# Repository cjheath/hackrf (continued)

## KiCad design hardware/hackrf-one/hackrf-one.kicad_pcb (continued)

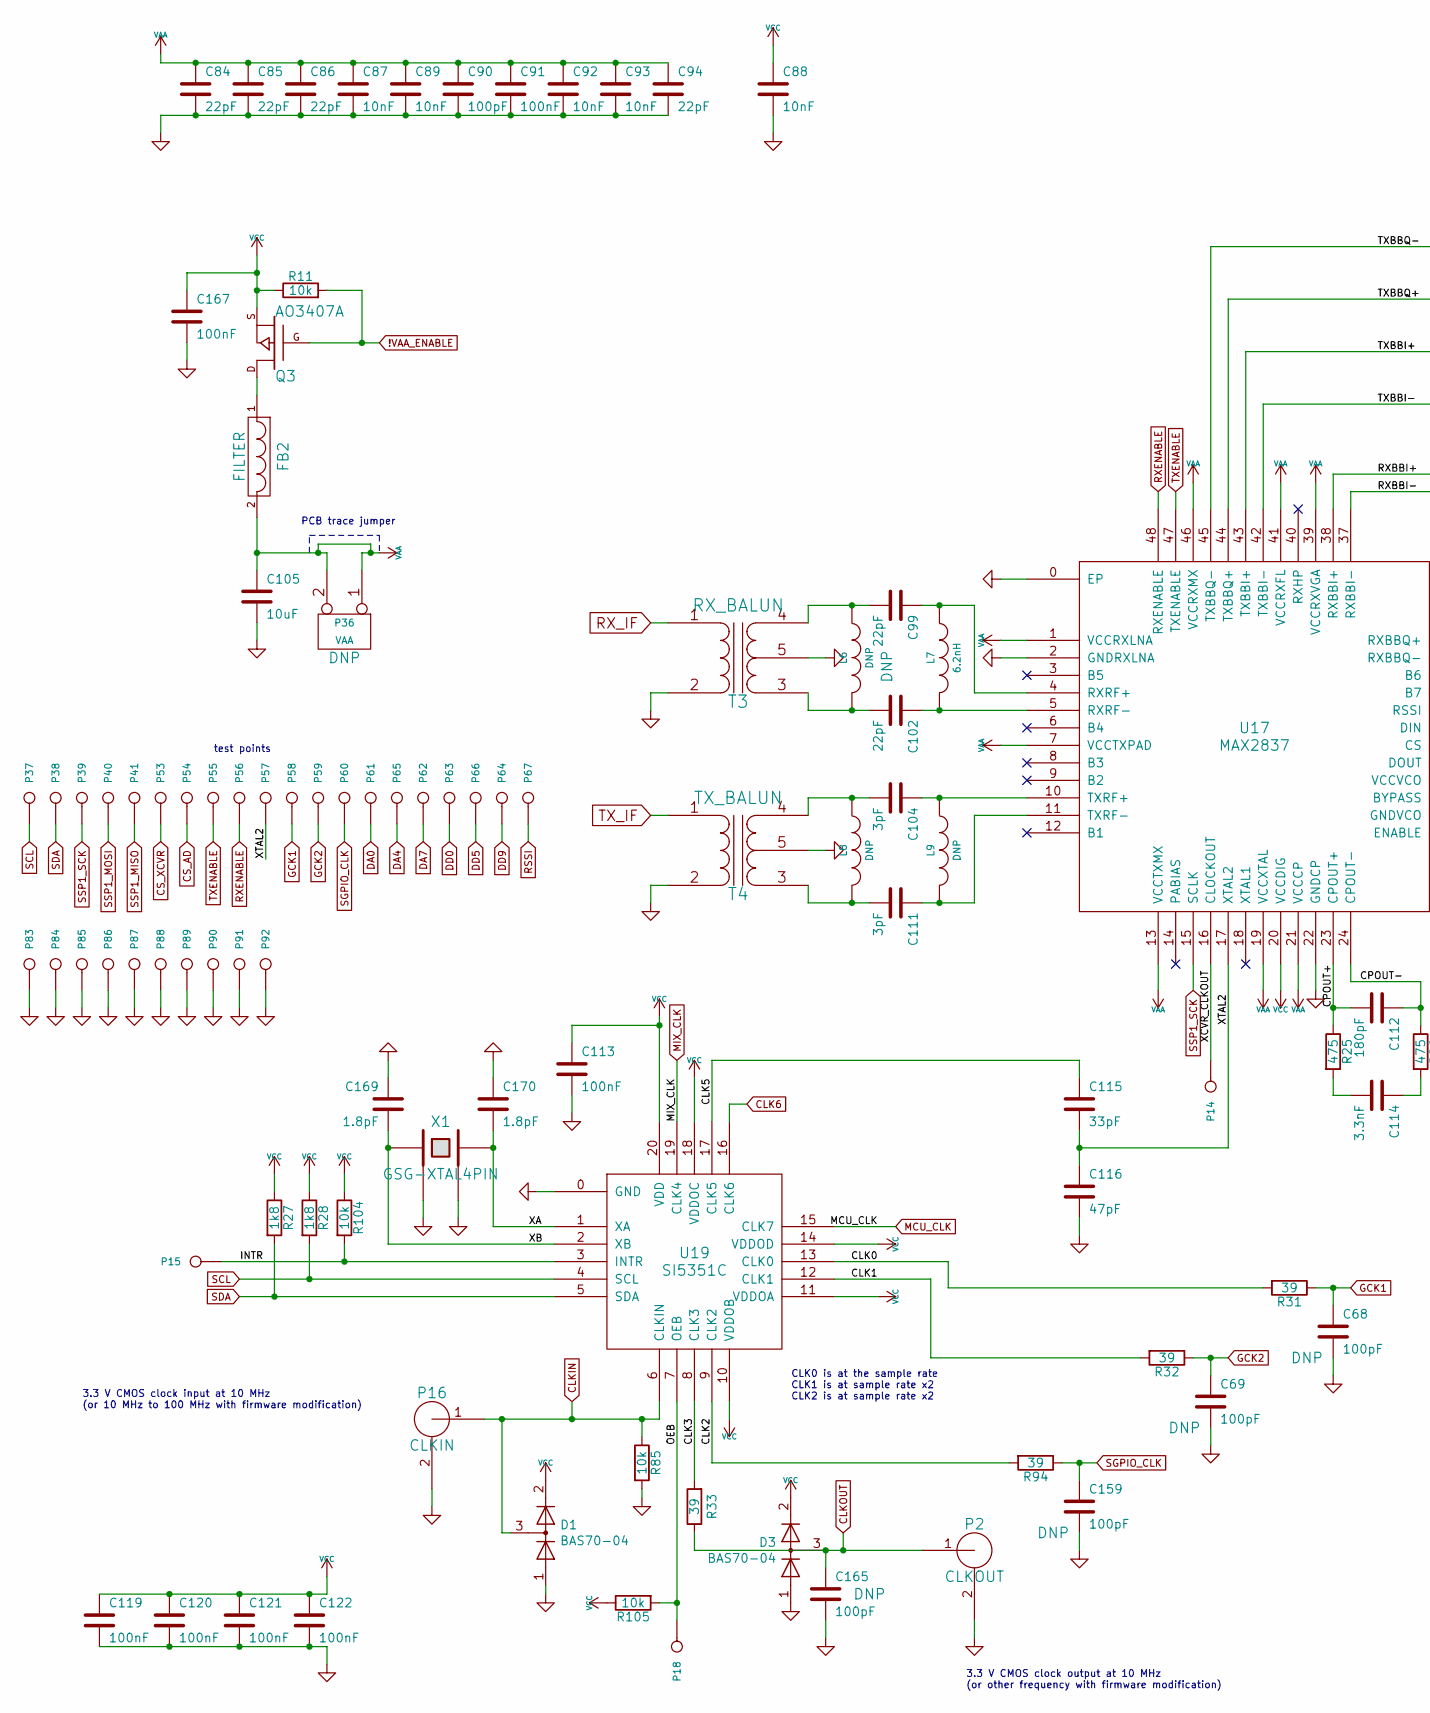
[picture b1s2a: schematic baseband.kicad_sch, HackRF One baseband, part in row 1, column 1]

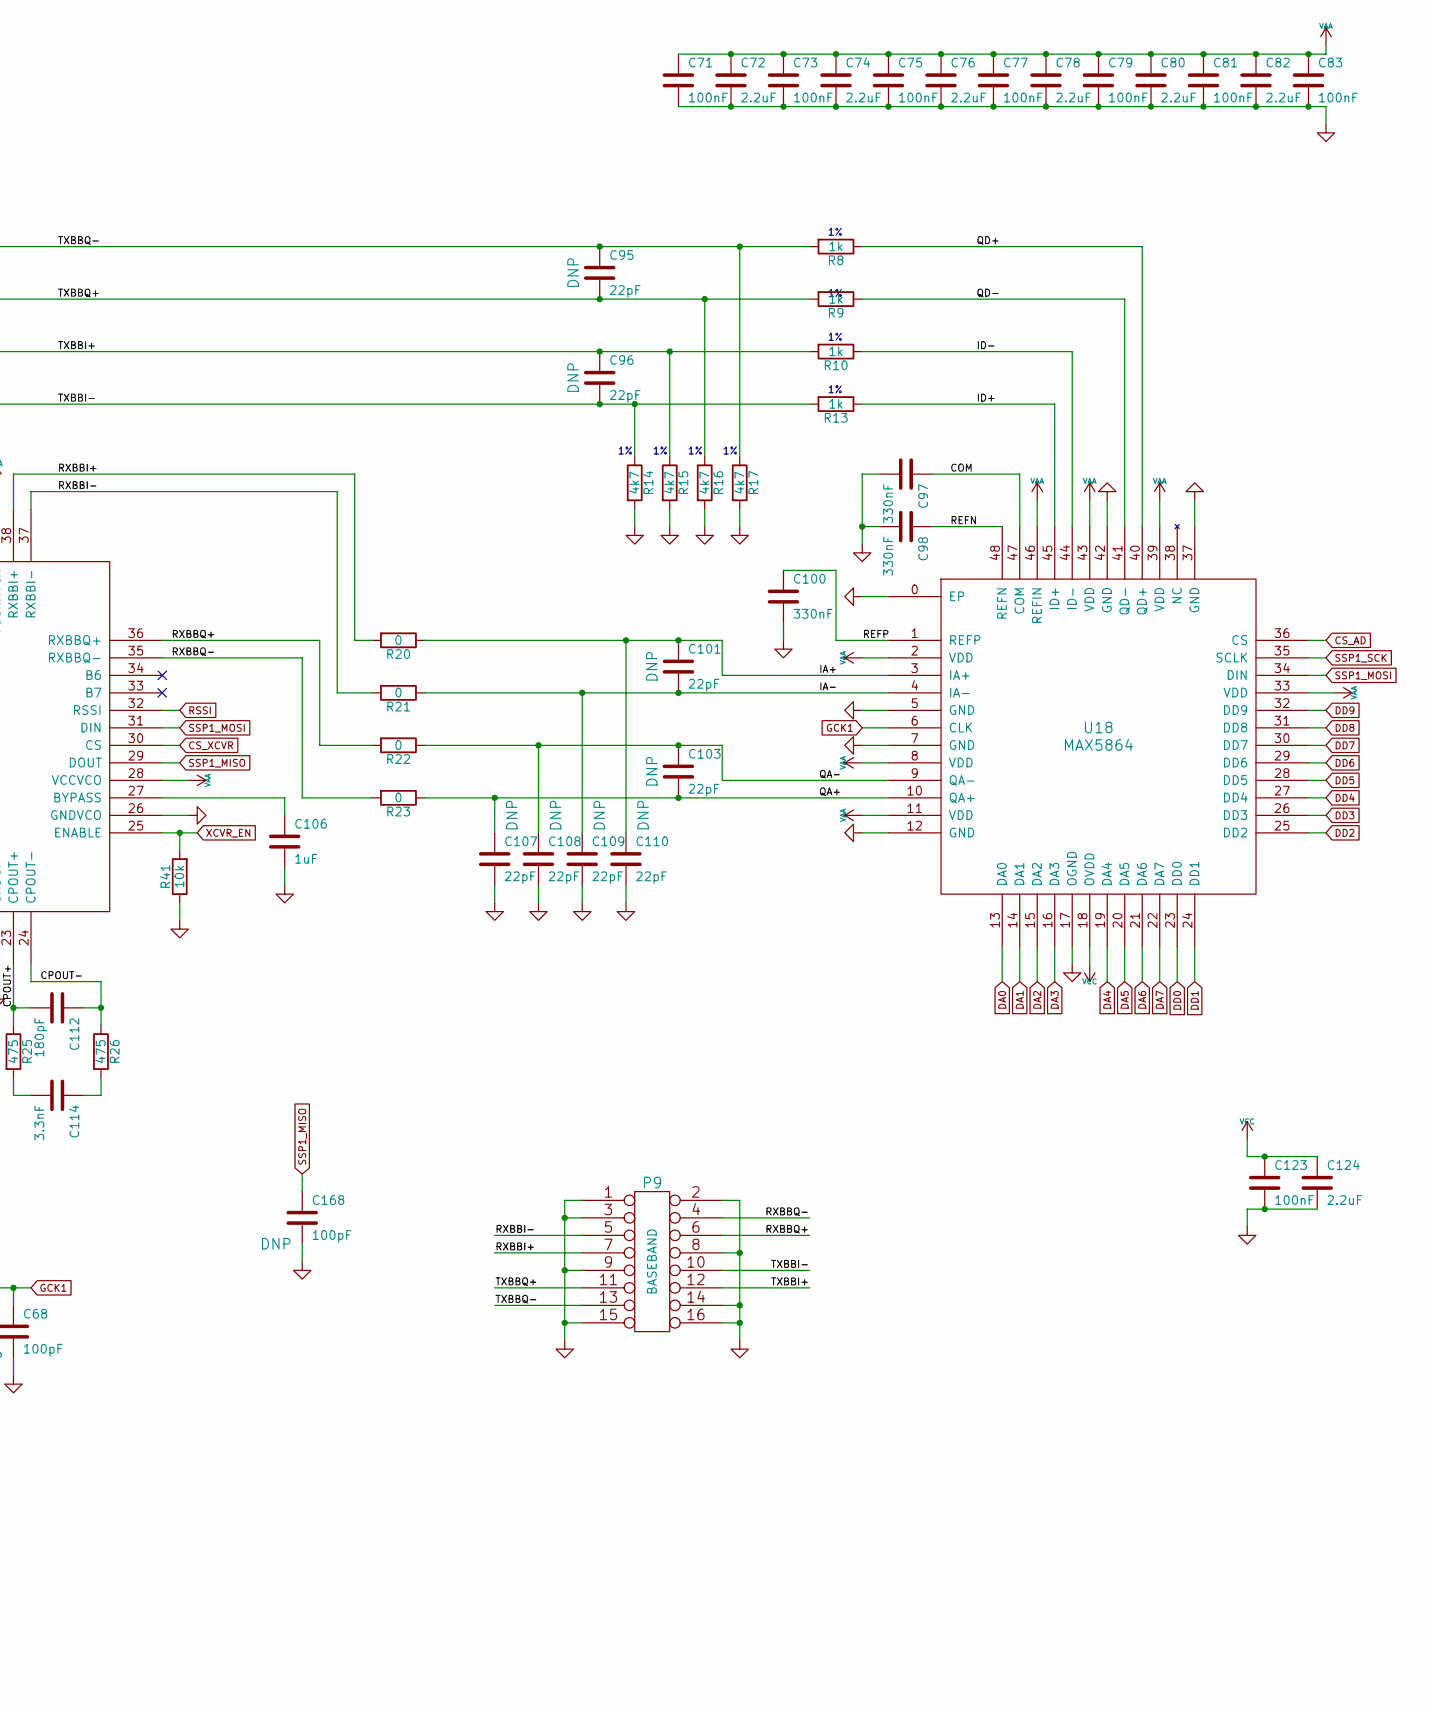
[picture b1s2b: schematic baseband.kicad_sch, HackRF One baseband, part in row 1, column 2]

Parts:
C68, C69, C90, C159, C165, C168: 100pF; GSG-0402; Part Number GRM1555C1H101JA01D
C71, C73, C75, C77, C79, C81, C83, C91, C113, C119, C120, C121, C122, C123, C167: 100nF; GSG-0402; Part Number GRM155R61A104KA01D
C72, C74, C76, C78, C80, C82, C124: 2.2uF; GSG-0402; Part Number LMK105BJ225MV-F
C84, C85, C86, C94, C95, C96, C99, C101, C102, C103, C107, C108, C109, C110: 22pF; GSG-0402; Part Number GRM1555C1H220JA01D
C87, C88, C89, C92, C93: 10nF; GSG-0402; Part Number GRM155R71C103KA01D
C97, C98, C100: 330nF; GSG-0402; Part Number GRM155R61A334KE15D
C104, C111: 3pF; GSG-0402; Part Number GRM1555C1H3R0CA01D
C105: 10uF; GSG-0805; Part Number GRM21BR61A106KE19L
C106: 1uF; GSG-0402; Part Number LMK105BJ105KV-F
C112: 180pF; GSG-0402; Part Number GRM1555C1H181JA01D
C114: 3.3nF; GSG-0402; Part Number GRM155R71H332KA01D
C115: 33pF; GSG-0402; Part Number GRM1555C1H330JA01D
C116: 47pF; GSG-0402; Part Number GRM1555C1H470JA01D
C169, C170: 1.8pF; GSG-0402; Part Number GRM1555C1E1R8BA01D
D1, D3: BAS70-04; SOT-23
FB2: FILTER; GSG-0805; Part Number BLM21PG221SN1D
L6, L8, L9: DNP; GSG-0402
L7: 6.2nH; GSG-0402; Part Number HK10056N2S-T
P2: CLKOUT; SMA-73251-2120; Part Number 73251-2121
P9: BASEBAND; GSG-HEADER-2x8; Part Number PPPC082LFBN-RC
P14: XCVR_CLKOUT; GSG-TESTPOINT-50MIL
P15: INTR; GSG-TESTPOINT-50MIL
P16: CLKIN; SMA-73251-2120; Part Number 73251-2121
P18: OEB; GSG-TESTPOINT-50MIL
P36: VAA; GSG-HEADER-1x2
P37: SCL; GSG-TESTPOINT-50MIL
P38: SDA; GSG-TESTPOINT-50MIL
P39: SSP1_SCK; GSG-TESTPOINT-50MIL
P40: SSP1_MOSI; GSG-TESTPOINT-50MIL
P41: SSP1_MISO; GSG-TESTPOINT-50MIL
P53: CS_XCVR; GSG-TESTPOINT-50MIL
P54: CS_AD; GSG-TESTPOINT-50MIL
P55: TXENABLE; GSG-TESTPOINT-50MIL
P56: RXENABLE; GSG-TESTPOINT-50MIL
P57: XTAL2; GSG-TESTPOINT-50MIL
P58: GCK1; GSG-TESTPOINT-50MIL
P59: GCK2; GSG-TESTPOINT-50MIL
P60: SGPIO_CLK; GSG-TESTPOINT-50MIL
P61: DA0; GSG-TESTPOINT-50MIL
P62: DA7; GSG-TESTPOINT-50MIL
P63: DD0; GSG-TESTPOINT-50MIL
P64: DD9; GSG-TESTPOINT-50MIL
P65: DA4; GSG-TESTPOINT-50MIL
P66: DD5; GSG-TESTPOINT-50MIL
P67: RSSI; GSG-TESTPOINT-50MIL
P83, P84, P85, P86, P87, P88, P89, P90, P91, P92: GND; GSG-TESTPOINT-50MIL
Q3: AO3407A; SOT23GDS; Part Number AO3407A
R8, R9, R10, R13: 1k; GSG-0402; Part Number RMCF0402FT1K00
R11, R41, R85, R104, R105: 10k; GSG-0402; Part Number RMCF0402JT10K0
R14, R15, R16, R17: 4k7; GSG-0402; Part Number RMCF0402FT4K70
R20, R21, R22, R23: 0; GSG-0402; Part Number RMCF0402ZT0R00
R25, R26: 475; GSG-0402; Part Number RMCF0402JT470R
R27, R28: 1k8; GSG-0402; Part Number RMCF0402JT1K80
R31, R32, R33, R94: 39; GSG-0402; Part Number RMCF0402JT39R0
T3: RX_BALUN; GSG-2500BL14M100; Part Number 2500BL14M100T
T4: TX_BALUN; GSG-2500BL14M100; Part Number 2500BL14M100T
U17: MAX2837; GSG-QFN48-6; Part Number MAX2837ETM+
U18: MAX5864; GSG-QFN48-7; Part Number MAX5864ETM+
U19: SI5351C; GSG-QFN20-4; Part Number SI5351C-B-GM
X1: GSG-XTAL4PIN; GSG-XTAL3.2x2.5mm; Part Number ABM8-25.000MHZ-10-D1G-T

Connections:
!VAA_ENABLE: Q3.G, R11.2; also elsewhere on the board
/baseband/CLK0: R31.2, U19.13 (CLK0)
/baseband/CLK1: R32.2, U19.12 (CLK1)
/baseband/CLK2: R94.2, U19.9 (CLK2)
/baseband/CLK3: R33.2, U19.8 (CLK3)
/baseband/CLK5: C115.1, U19.17 (CLK5)
/baseband/COM: C97.1, U18.47 (COM)
/baseband/CPOUT+: C112.2, R25.1, U17.23 (CPOUT+)
/baseband/CPOUT-: C112.1, R26.1, U17.24 (CPOUT-)
/baseband/IA+: C101.1, C110.1, R20.1, U18.3 (IA+)
/baseband/IA-: C101.2, C109.1, R21.1, U18.4 (IA-)
/baseband/ID+: R13.1, U18.45 (ID+)
/baseband/ID-: R10.1, U18.44 (ID-)
/baseband/INTR: P15.1, R104.2, U19.3 (INTR)
/baseband/OEB: P18.1, R105.2, U19.7 (OEB)
/baseband/QA+: C103.2, C107.1, R23.1, U18.10 (QA+)
/baseband/QA-: C103.1, C108.1, R22.1, U18.9 (QA-)
/baseband/QD+: R8.1, U18.40 (QD+)
/baseband/QD-: R9.1, U18.41 (QD-)
/baseband/REFN: C98.1, U18.48 (REFN)
/baseband/REFP: C100.1, U18.1 (REFP)
/baseband/RXBBI+: P9.7, R20.2, U17.38 (RXBBI+)
/baseband/RXBBI-: P9.5, R21.2, U17.37 (RXBBI-)
/baseband/RXBBQ+: P9.6, R22.2, U17.36 (RXBBQ+)
/baseband/RXBBQ-: P9.4, R23.2, U17.35 (RXBBQ-)
/baseband/TXBBI+: C96.1, P9.12, R10.2, R15.1, U17.43 (TXBBI+)
/baseband/TXBBI-: C96.2, P9.10, R13.2, R14.1, U17.42 (TXBBI-)
/baseband/TXBBQ+: C95.2, P9.11, R9.2, R16.1, U17.44 (TXBBQ+)
/baseband/TXBBQ-: C95.1, P9.13, R8.2, R17.1, U17.45 (TXBBQ-)
/baseband/XA: C170.2, U19.1 (XA), X1.3
/baseband/XB: C169.2, U19.2 (XB), X1.1
/baseband/XCVR_CLKOUT: P14.1, U17.16 (CLOCKOUT)
/baseband/XTAL2: C115.2, C116.1, P57.1, U17.17 (XTAL2)
CLK6: U19.16 (CLK6); also elsewhere on the board
CLKIN: D1.3 (K), P16.1 (RF), R85.1, U19.6 (CLKIN); also elsewhere on the board
CLKOUT: C165.1, D3.3 (K), P2.1 (RF), R33.1; also elsewhere on the board
CS_AD: P54.1, U18.36 (CS); also elsewhere on the board
CS_XCVR: P53.1, U17.30 (CS); also elsewhere on the board
DA0: P61.1, U18.13 (DA0); also elsewhere on the board
DA1: U18.14 (DA1); also elsewhere on the board
DA2: U18.15 (DA2); also elsewhere on the board
DA3: U18.16 (DA3); also elsewhere on the board
DA4: P65.1, U18.19 (DA4); also elsewhere on the board
DA5: U18.20 (DA5); also elsewhere on the board
DA6: U18.21 (DA6); also elsewhere on the board
DA7: P62.1, U18.22 (DA7); also elsewhere on the board
DD0: P63.1, U18.23 (DD0); also elsewhere on the board
DD1: U18.24 (DD1); also elsewhere on the board
DD2: U18.25 (DD2); also elsewhere on the board
DD3: U18.26 (DD3); also elsewhere on the board
DD4: U18.27 (DD4); also elsewhere on the board
DD5: P66.1, U18.28 (DD5); also elsewhere on the board
DD6: U18.29 (DD6); also elsewhere on the board
DD7: U18.30 (DD7); also elsewhere on the board
DD8: U18.31 (DD8); also elsewhere on the board
DD9: P64.1, U18.32 (DD9); also elsewhere on the board
GCK1: C68.1, P58.1, R31.1, U18.6 (CLK); also elsewhere on the board
GCK2: C69.1, P59.1, R32.1; also elsewhere on the board
GND: C68.2, C69.2, C71.2, C72.2, C73.2, C74.2, C75.2, C76.2, C77.2, C78.2, C79.2, C80.2, C81.2, C82.2, C83.2, C84.2, C85.2, C86.2, C87.2, C88.2, C89.2, C90.2, C91.2, C92.2, C93.2, C94.2, C97.2, C98.2, C100.2, C105.2, C106.2, C107.2, C108.2, C109.2, C110.2, C113.2, C116.2, C119.2, C120.2, C121.2, C122.2, C123.2, C124.2, C159.2, C165.2, C167.2, C168.2, C169.1, C170.1, D1.1 (K), D3.1 (K), P2.2 (GND), P9.1, P9.2, P9.3, P9.8, P9.9, P9.14, P9.15, P9.16, P16.2 (GND), P83.1, P84.1, P85.1, P86.1, P87.1, P88.1, P89.1, P90.1, P91.1, P92.1, R14.2, R15.2, R16.2, R17.2, R41.1, R85.2, T3.2 (S2), T3.5 (PM), T4.2 (S2), T4.5 (PM), U17.0 (EP), U17.2 (GNDRXLNA), U17.22 (GNDCP), U17.26 (GNDVCO), U18.0 (EP), U18.5 (GND), U18.7 (GND), U18.12 (GND), U18.17 (OGND), U18.37 (GND), U18.42 (GND), U19.0 (GND), X1.2, X1.4; also elsewhere on the board
MCU_CLK: U19.15 (CLK7); also elsewhere on the board
MIX_CLK: U19.19 (CLK4); also elsewhere on the board
unnamed: C114.1, R26.2
unnamed: C114.2, R25.2
unnamed: FB2.1, Q3.D
unnamed: C102.2, L6.2, T3.3 (PR1)
unnamed: C99.2, L6.1, T3.4 (PR2)
unnamed: C111.2, L8.2, T4.3 (PR1)
unnamed: C104.2, L8.1, T4.4 (PR2)
unnamed: C106.1, U17.27 (BYPASS)
unnamed: C99.1, L7.1, U17.4 (RXRF+)
unnamed: C102.1, L7.2, U17.5 (RXRF-)
unnamed: C104.1, L9.1, U17.10 (TXRF+)
unnamed: C111.1, L9.2, U17.11 (TXRF-)
RSSI: P67.1, U17.32 (RSSI); also elsewhere on the board
RXENABLE: P56.1, U17.48 (RXENABLE); also elsewhere on the board
RX_IF: T3.1 (S1); also elsewhere on the board
SCL: P37.1, R28.2, U19.4 (SCL); also elsewhere on the board
SDA: P38.1, R27.2, U19.5 (SDA); also elsewhere on the board
SGPIO_CLK: C159.1, P60.1, R94.1; also elsewhere on the board
SSP1_MISO: C168.1, P41.1, U17.29 (DOUT); also elsewhere on the board
SSP1_MOSI: P40.1, U17.31 (DIN), U18.34 (DIN); also elsewhere on the board
SSP1_SCK: P39.1, U17.15 (SCLK), U18.35 (SCLK); also elsewhere on the board
TXENABLE: P55.1, U17.47 (TXENABLE); also elsewhere on the board
TX_IF: T4.1 (S1); also elsewhere on the board
VAA: C71.1, C72.1, C73.1, C74.1, C75.1, C76.1, C77.1, C78.1, C79.1, C80.1, C81.1, C82.1, C83.1, C84.1, C85.1, C86.1, C87.1, C89.1, C90.1, C91.1, C92.1, C93.1, C94.1, C105.1, FB2.2, P36.1, P36.2 (PM), U17.1 (VCCRXLNA), U17.7 (VCCTXPAD), U17.13 (VCCTXMX), U17.19 (VCCXTAL), U17.21 (VCCCP), U17.28 (VCCVCO), U17.39 (VCCRXVGA), U17.41 (VCCRXFL), U17.46 (VCCRXMX), U18.2 (VDD), U18.8 (VDD), U18.11 (VDD), U18.33 (VDD), U18.39 (VDD), U18.43 (VDD), U18.46 (REFIN); also elsewhere on the board
VCC: C88.1, C113.1, C119.1, C120.1, C121.1, C122.1, C123.1, C124.1, C167.1, D1.2 (A), D3.2 (A), Q3.S, R11.1, R27.1, R28.1, R104.1, R105.1, U17.20 (VCCDIG), U18.18 (OVDD), U19.10 (VDDOB), U19.11 (VDDOA), U19.14 (VDDOD), U19.18 (VDDOC), U19.20 (VDD); also elsewhere on the board
XCVR_EN: R41.2, U17.25 (ENABLE); also elsewhere on the board

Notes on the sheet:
test points
3.3 V CMOS clock input at 10 MHz (or 10 MHz to 100 MHz with firmware modification)
3.3 V CMOS clock output at 10 MHz (or other frequency with firmware modification)
PCB trace jumper
CLK0 is at the sample rate CLK1 is at sample rate x2 CLK2 is at sample rate x2

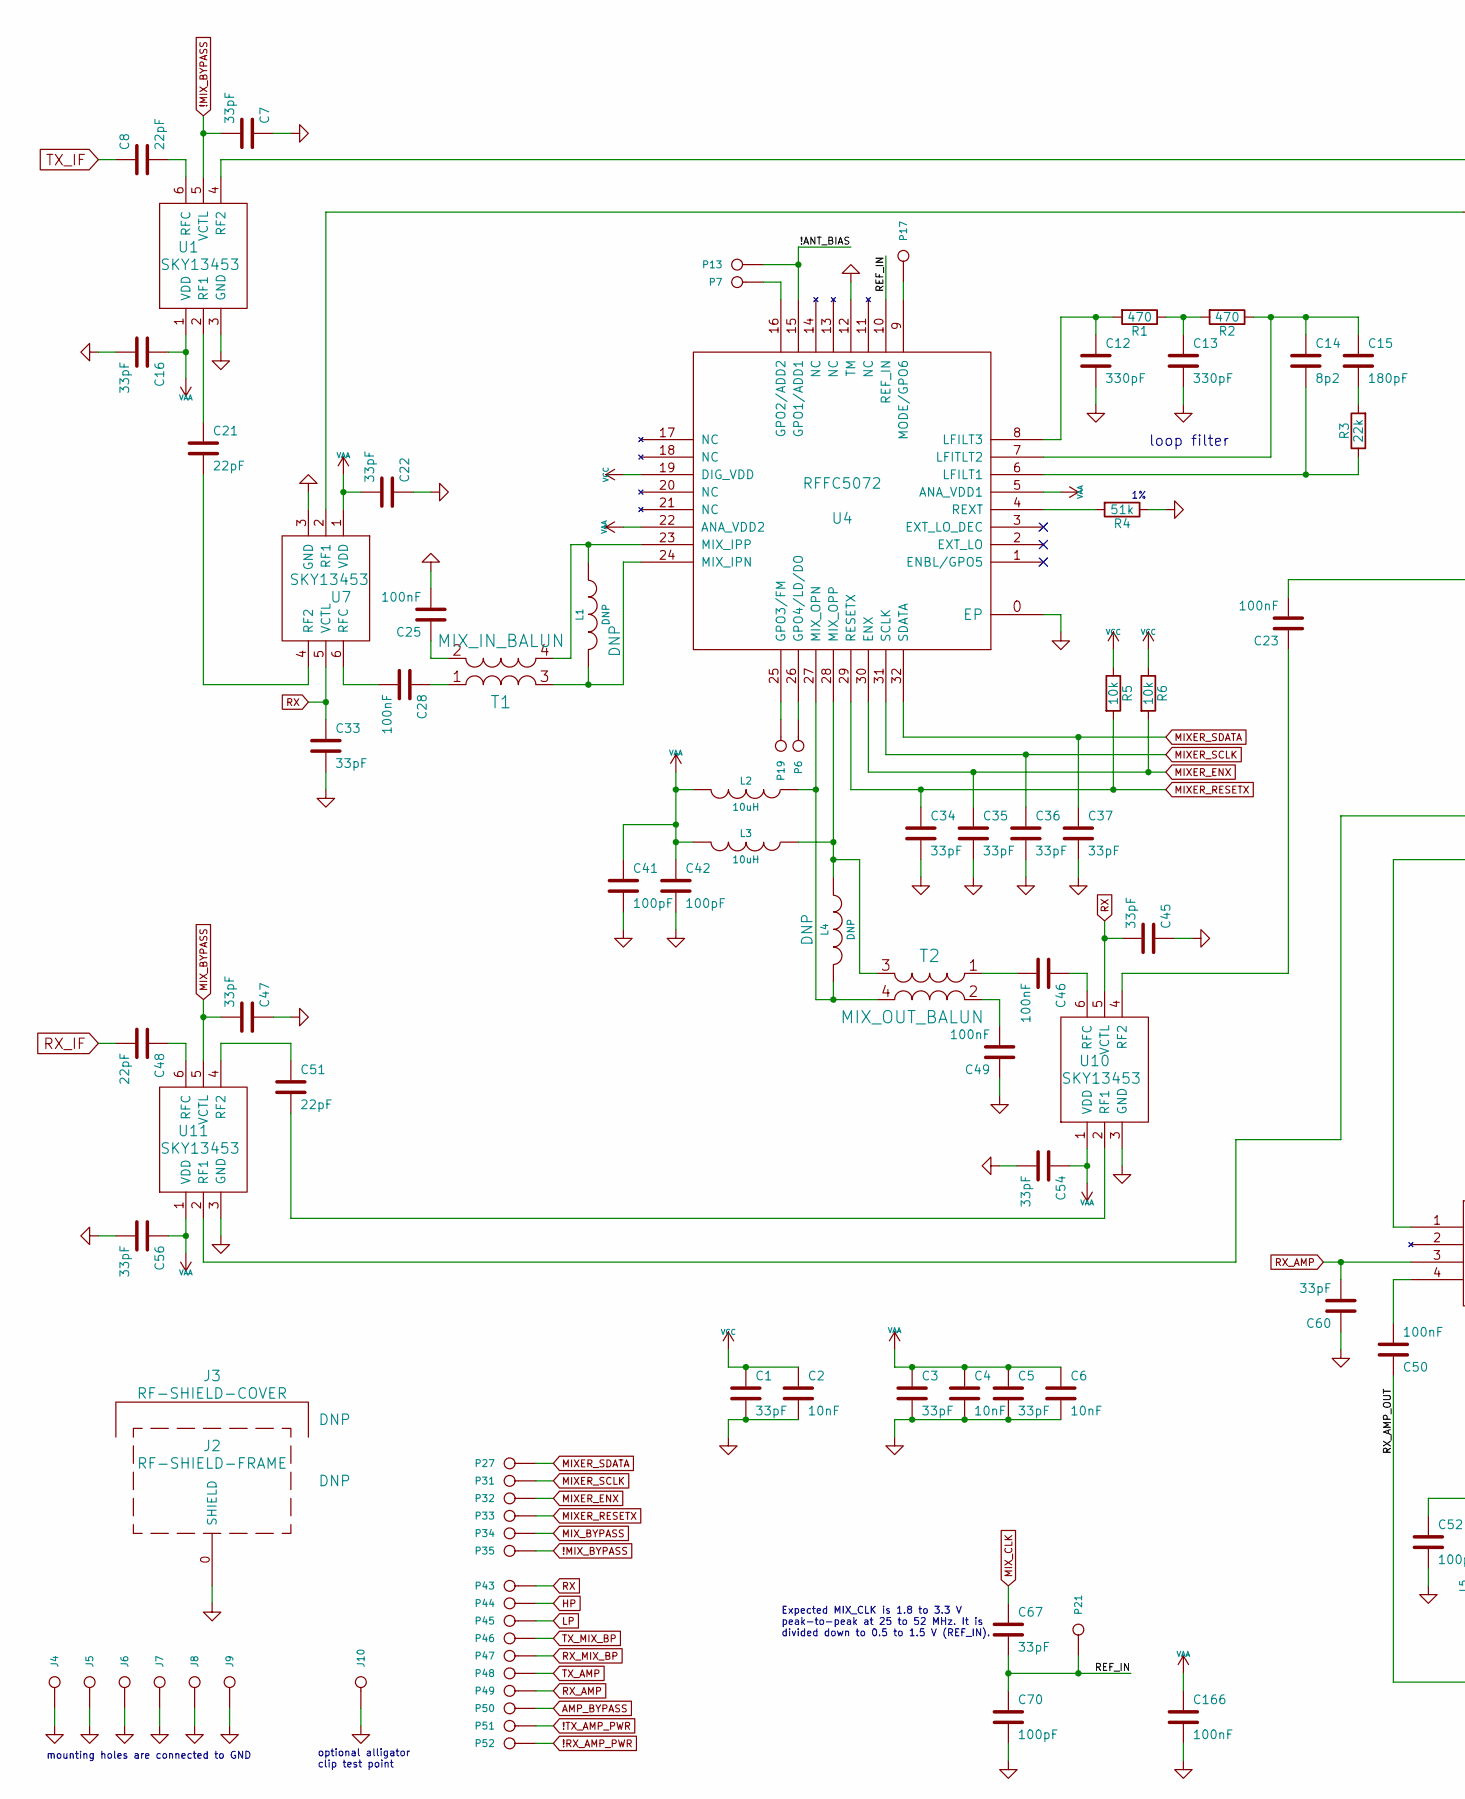
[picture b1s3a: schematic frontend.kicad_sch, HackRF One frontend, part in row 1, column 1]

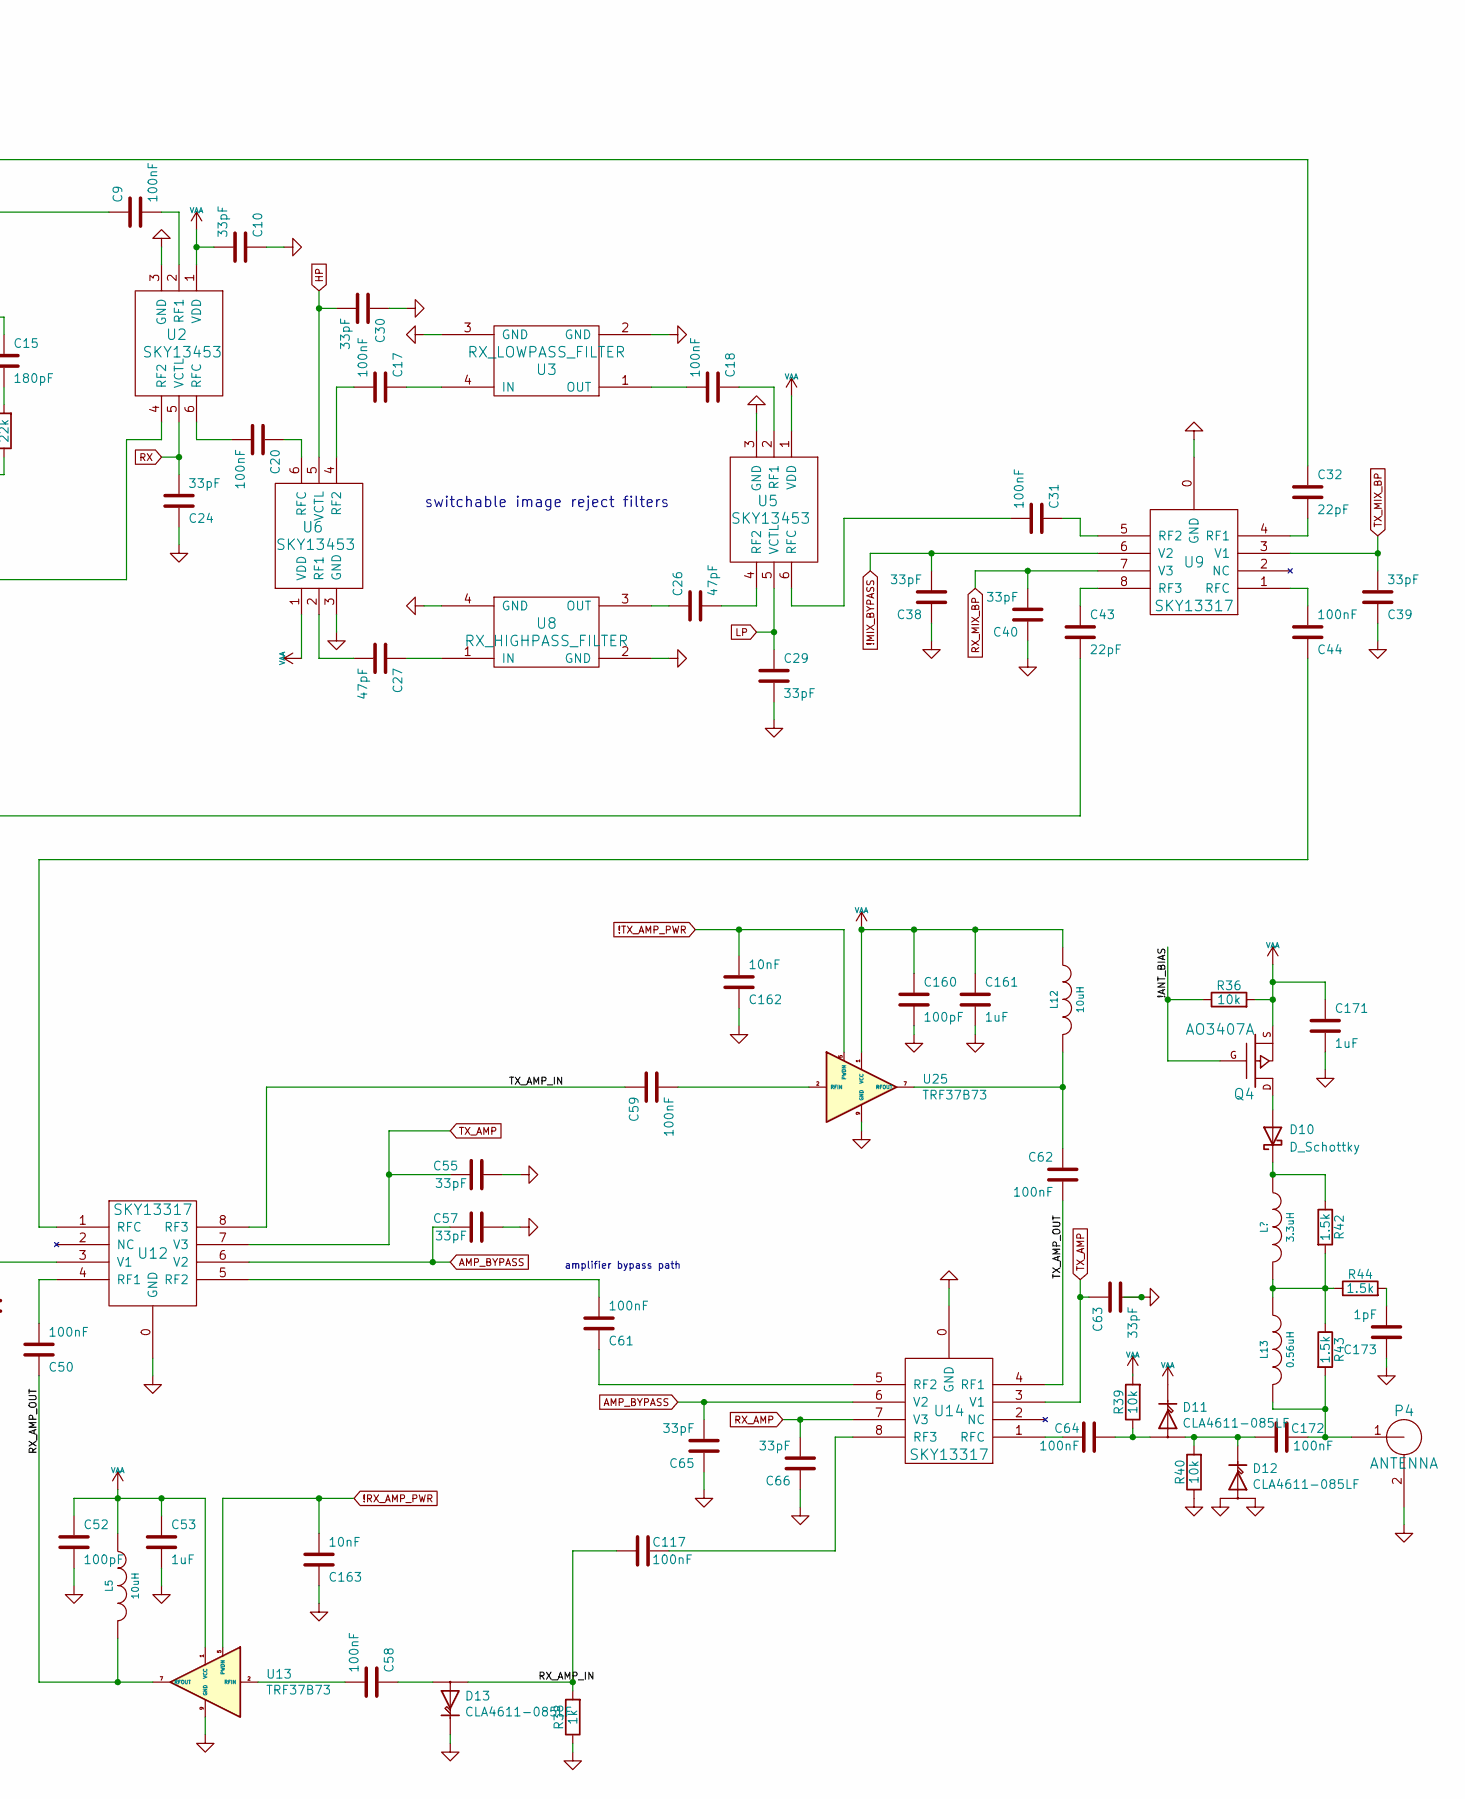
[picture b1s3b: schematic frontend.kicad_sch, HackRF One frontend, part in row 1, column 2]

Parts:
C1, C3, C5, C7, C10, C16, C22, C24, C29, C30, C33, C34, C35, C36, C37, C38, C39, C40, C45, C47, C54, C55, C56, C57, C60, C63, C65, C66, C67: 33pF; GSG-0402; Part Number GRM1555C1H330JA01D
C2, C4, C6, C162, C163: 10nF; GSG-0402; Part Number GRM155R71C103KA01D
C8, C21, C32, C43, C48, C51: 22pF; GSG-0402; Part Number GRM1555C1H220JA01D
C9, C17, C18, C20, C23, C25, C28, C31, C44, C46, C49, C50, C58, C59, C61, C62, C64, C117, C166, C172: 100nF; GSG-0402; Part Number GRM155R61A104KA01D
C12, C13: 330pF; GSG-0402; Part Number GRM155R71H331KA01D
C14: 8p2; GSG-0402; Part Number UMK105CG8R2DV-F
C15: 180pF; GSG-0402; Part Number GRM1555C1H181JA01D
C26, C27: 47pF; GSG-0402; Part Number GRM1555C1H470JA01D
C41, C42, C52, C70, C160: 100pF; GSG-0402; Part Number GRM1555C1H101JA01D
C53, C161, C171: 1uF; GSG-0402; Part Number LMK105BJ105KV-F
C173: 1pF; GSG-0402; Part Number GJM1555C1H1R0JB01
D10: D_Schottky; DSN1006-2; Part Number PMEG4010ESBYL
D11, D12, D13: CLA4611-085LF; SkyworksLimiterDiode; Part Number CLA4611-085LF
J2: RF-SHIELD-FRAME; GSG-SHIELD-BMI-S-230; Part Number BMI-S-230-F-R
J3: RF-SHIELD-COVER; GSG-NULL-MODULE; Part Number BMI-S-230-C
J4, J5, J6, J7, J8, J9: MOUNTING_HOLE; GSG-HOLE126MIL-COPPER
J10: GND_CLIP; GSG-TEST-POINT-S1751-46R; Part Number S1751-46R
L1, L4: DNP; GSG-0402
L2, L3, L5, L12: 10uH; GSG-0603; Part Number BRL1608T100M
L13: 0.56uH; GSG-0603; Part Number SDWL1608CR56JSTF
L14: 3.3uH; GSG-0603; Part Number BRL1608T3R3M
P4: ANTENNA; SMA-73251-2120; Part Number 73251-2121
P6: GPO4; GSG-TESTPOINT-50MIL
P7: GPO2; GSG-TESTPOINT-50MIL
P13: GPO1; GSG-TESTPOINT-50MIL
P17: GPO6; GSG-TESTPOINT-50MIL
P19: GPO3; GSG-TESTPOINT-50MIL
P21: REF_IN; GSG-TESTPOINT-50MIL
P27: MIXER_SDATA; GSG-TESTPOINT-50MIL
P31: MIXER_SCLK; GSG-TESTPOINT-50MIL
P32: MIXER_ENX; GSG-TESTPOINT-50MIL
P33: MIXER_RESETX; GSG-TESTPOINT-50MIL
P34: MIX_BYPASS; GSG-TESTPOINT-50MIL
P35: !MIX_BYPASS; GSG-TESTPOINT-50MIL
P43: RX; GSG-TESTPOINT-50MIL
P44: HP; GSG-TESTPOINT-50MIL
P45: LP; GSG-TESTPOINT-50MIL
P46: TX_MIX_BP; GSG-TESTPOINT-50MIL
P47: RX_MIX_BP; GSG-TESTPOINT-50MIL
P48: TX_AMP; GSG-TESTPOINT-50MIL
P49: RX_AMP; GSG-TESTPOINT-50MIL
P50: AMP_BYPASS; GSG-TESTPOINT-50MIL
P51: !TX_AMP_PWR; GSG-TESTPOINT-50MIL
P52: !RX_AMP_PWR; GSG-TESTPOINT-50MIL
Q4: AO3407A; SOT23GDS; Part Number AO3407A
R1, R2: 470; GSG-0402; Part Number RMCF0402JT470R
R3: 22k; GSG-0402; Part Number ERJ-2GEJ223X
R4: 51k; GSG-0402; Part Number RMCF0402FT51K0
R5, R6, R36, R39, R40: 10k; GSG-0402; Part Number RMCF0402JT10K0
R38: 1k; GSG-0402; Part Number RMCF0402JT10K0
R42, R43, R44: 1.5k; GSG-0402; Part Number ERJ-2GEJ152X
T1: MIX_IN_BALUN; GSG-B0310J50100AHF; Part Number B0310J50100AHF
T2: MIX_OUT_BALUN; GSG-B0310J50100AHF; Part Number B0310J50100AHF
U1, U2, U5, U6, U7, U10, U11: SKY13453; SKY13453-385LF
U3: RX_LOWPASS_FILTER; GSG-LP0603; Part Number LP0603A1880ANTR
U4: RFFC5072; GSG-QFN32; Part Number RFFC5072TR7
U8: RX_HIGHPASS_FILTER; GSG-HP-DEA; Part Number DEA162400HT-8004B1
U9, U12, U14: SKY13317; GSG-SKY13317-373LF; Part Number SKY13317-373LF
U13, U25: TRF37B73; WSON-8-1EP_2x2mm_P0.5mm_EP0.9x1.6mm

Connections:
!MIX_BYPASS: C7.2, C38.2, P35.1, U1.5 (VCTL), U9.6 (V2); also elsewhere on the board
!RX_AMP_PWR: C163.2, P52.1, U13.5 (PWDN); also elsewhere on the board
!TX_AMP_PWR: C162.2, P51.1, U25.5 (PWDN); also elsewhere on the board
/frontend/!ANT_BIAS: P13.1, Q4.G, R36.1, U4.15 (GPO1/ADD1)
/frontend/REF_IN: C67.2, C70.1, P21.1, U4.10 (REF_IN)
/frontend/RX_AMP_IN: C117.2, D13.1 (A1), R38.2
/frontend/RX_AMP_OUT: C50.1, L5.2, U13.7 (RFOUT)
/frontend/TX_AMP_IN: C59.1, U12.8 (RF3)
/frontend/TX_AMP_OUT: C62.2, U14.4 (RF1)
AMP_BYPASS: C57.1, C65.2, P50.1, U12.6 (V2), U14.6 (V2); also elsewhere on the board
GND: C1.2, C2.2, C3.2, C4.2, C5.2, C6.2, C7.1, C10.1, C12.2, C13.2, C16.2, C22.1, C24.1, C25.2, C29.2, C30.1, C33.2, C34.2, C35.2, C36.2, C37.2, C38.1, C39.1, C40.1, C41.2, C42.2, C45.1, C47.1, C49.1, C52.2, C53.2, C54.2, C55.2, C56.2, C57.2, C60.1, C63.2, C65.1, C66.1, C70.2, C160.2, C161.2, C162.1, C163.1, C166.2, C171.2, C173.1, D12.1 (A1), D12.3 (A2), D13.2 (K), J2.0 (SHIELD), J4.1, J5.1, J6.1, J7.1, J8.1, J9.1, J10.1, P4.2 (GND), R4.1, R38.1, R40.1, U1.3 (GND), U2.3 (GND), U3.2 (GND), U3.3 (GND), U4.0 (EP), U4.12 (TM), U5.3 (GND), U6.3 (GND), U7.3 (GND), U8.2 (GND), U8.4 (GND), U9.0 (GND), U10.3 (GND), U11.3 (GND), U12.0 (GND), U13.9 (GND), U14.0 (GND), U25.9 (GND); also elsewhere on the board
HP: C30.2, P44.1, U6.5 (VCTL); also elsewhere on the board
LP: C29.1, P45.1, U5.5 (VCTL); also elsewhere on the board
MIXER_ENX: C35.1, P32.1, R6.2, U4.30 (ENX); also elsewhere on the board
MIXER_RESETX: C34.1, P33.1, R5.2, U4.29 (RESETX); also elsewhere on the board
MIXER_SCLK: C36.1, P31.1, U4.31 (SCLK); also elsewhere on the board
MIXER_SDATA: C37.1, P27.1, U4.32 (SDATA); also elsewhere on the board
MIX_BYPASS: C47.2, P34.1, U11.5 (VCTL); also elsewhere on the board
MIX_CLK: C67.1; also elsewhere on the board
unnamed: C13.1, R1.1, R2.2
unnamed: C15.2, R3.2
unnamed: C173.2, R44.2
unnamed: D10.2 (A), Q4.D
unnamed: D10.1 (K), L14.1, R42.1
unnamed: C64.2, D11.1 (A1), R39.1
unnamed: C172.1, D11.3 (A2), D12.2 (K), R40.2
unnamed: C58.1, D13.3 (A2)
unnamed: L13.1, L14.2, R42.2, R43.1, R44.1
unnamed: C172.2, L13.2, P4.1 (RF), R43.2
unnamed: L1.2, T1.3 (PR1), U4.24 (MIX_IPN)
unnamed: L1.1, T1.4 (PR2), U4.23 (MIX_IPP)
unnamed: C28.1, T1.1 (S1)
unnamed: C25.1, T1.2 (S2)
unnamed: L3.1, L4.1, T2.3 (PR1), U4.28 (MIX_OPP)
unnamed: L2.1, L4.2, T2.4 (PR2), U4.27 (MIX_OPN)
unnamed: C46.2, T2.1 (S1)
unnamed: C49.2, T2.2 (S2)
unnamed: C21.1, U1.2 (RF1)
unnamed: C32.1, U1.4 (RF2)
unnamed: C8.2, U1.6 (RFC)
unnamed: C9.2, U2.2 (RF1)
unnamed: C23.2, U2.4 (RF2)
unnamed: C20.2, U2.6 (RFC)
unnamed: C17.1, U3.4 (IN)
unnamed: C18.2, U3.1 (OUT)
unnamed: P7.1, U4.16 (GPO2/ADD2)
unnamed: P19.1, U4.25 (GPO3/FM)
unnamed: P6.1, U4.26 (GPO4/LD/DO)
unnamed: C14.2, R3.1, U4.6 (LFILT1)
unnamed: C12.1, R1.2, U4.8 (LFILT3)
unnamed: C14.1, C15.1, R2.1, U4.7 (LFITLT2)
unnamed: P17.1, U4.9 (MODE/GPO6)
unnamed: R4.2, U4.4 (REXT)
unnamed: C18.1, U5.2 (RF1)
unnamed: C26.2, U5.4 (RF2)
unnamed: C31.2, U5.6 (RFC)
unnamed: C27.2, U6.2 (RF1)
unnamed: C17.2, U6.4 (RF2)
unnamed: C20.1, U6.6 (RFC)
unnamed: C9.1, U7.2 (RF1)
unnamed: C21.2, U7.4 (RF2)
unnamed: C28.2, U7.6 (RFC)
unnamed: C27.1, U8.1 (IN)
unnamed: C26.1, U8.3 (OUT)
unnamed: C32.2, U9.4 (RF1)
unnamed: C31.1, U9.5 (RF2)
unnamed: C43.1, U9.8 (RF3)
unnamed: C44.2, U9.1 (RFC)
unnamed: C51.2, U10.2 (RF1)
unnamed: C23.1, U10.4 (RF2)
unnamed: C46.1, U10.6 (RFC)
unnamed: C43.2, U11.2 (RF1)
unnamed: C51.1, U11.4 (RF2)
unnamed: C48.1, U11.6 (RFC)
unnamed: C50.2, U12.4 (RF1)
unnamed: C61.2, U12.5 (RF2)
unnamed: C44.1, U12.1 (RFC)
unnamed: C58.2, U13.2 (RFIN)
unnamed: C61.1, U14.5 (RF2)
unnamed: C117.1, U14.8 (RF3)
unnamed: C64.1, U14.1 (RFC)
unnamed: C59.2, U25.2 (RFIN)
unnamed: C62.1, L12.2, U25.7 (RFOUT)
RX: C24.2, C33.1, C45.2, P43.1, U2.5 (VCTL), U7.5 (VCTL), U10.5 (VCTL); also elsewhere on the board
RX_AMP: C60.2, C66.2, P49.1, U12.3 (V1), U14.7 (V3); also elsewhere on the board
RX_IF: C48.2; also elsewhere on the board
RX_MIX_BP: C40.2, P47.1, U9.7 (V3); also elsewhere on the board
TX_AMP: C55.1, C63.1, P48.1, U12.7 (V3), U14.3 (V1); also elsewhere on the board
TX_IF: C8.1; also elsewhere on the board
TX_MIX_BP: C39.2, P46.1, U9.3 (V1); also elsewhere on the board
VAA: C3.1, C4.1, C5.1, C6.1, C10.2, C16.1, C22.2, C41.1, C42.1, C52.1, C53.1, C54.1, C56.1, C160.1, C161.1, C166.1, C171.1, D11.2 (K), L2.2, L3.2, L5.1, L12.1, Q4.S, R36.2, R39.2, U1.1 (VDD), U2.1 (VDD), U4.5 (ANA_VDD1), U4.22 (ANA_VDD2), U5.1 (VDD), U6.1 (VDD), U7.1 (VDD), U10.1 (VDD), U11.1 (VDD), U13.1 (VCC), U25.1 (VCC); also elsewhere on the board
VCC: C1.1, C2.1, R5.1, R6.1, U4.19 (DIG_VDD); also elsewhere on the board

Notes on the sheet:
amplifier bypass path
switchable image reject filters
loop filter
Expected MIX_CLK is 1.8 to 3.3 V peak-to-peak at 25 to 52 MHz. It is divided down to 0.5 to 1.5 V (REF_IN).
optional alligator clip test point
mounting holes are connected to GND

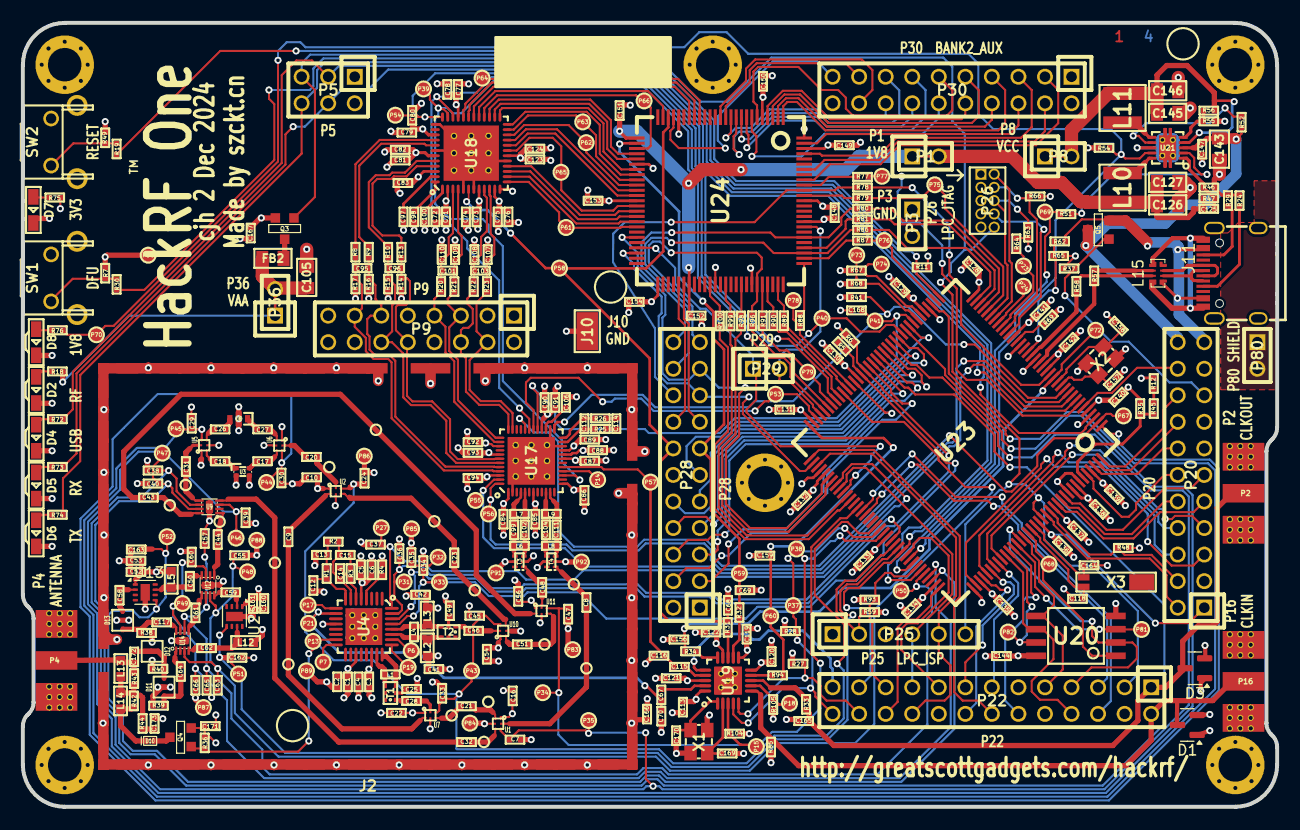
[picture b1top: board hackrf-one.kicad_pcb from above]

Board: 4 copper layers, 120.0 x 75.0 mm, 437 parts (0 on the bottom side), 319 nets.

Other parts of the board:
MARK1MM, MARK1MM#2, MARK1MM#3: VAL**; GSG-MARK1MM
TESTPOINT-30MIL-MASKONLY, TESTPOINT-30MIL-MASKONLY#2, TESTPOINT-30MIL-MASKONLY#3, TESTPOINT-30MIL-MASKONLY#4, TESTPOINT-30MIL-MASKONLY#5, TESTPOINT-30MIL-MASKONLY#6, TESTPOINT-30MIL-MASKONLY#7, TESTPOINT-30MIL-MASKONLY#8, TESTPOINT-30MIL-MASKONLY#9, TESTPOINT-30MIL-MASKONLY#10, TESTPOINT-30MIL-MASKONLY#11, TESTPOINT-30MIL-MASKONLY#12, TESTPOINT-30MIL-MASKONLY#13, TESTPOINT-30MIL-MASKONLY#14, TESTPOINT-30MIL-MASKONLY#15: VAL**; GSG-TESTPOINT-30MIL-MASKONLY

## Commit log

2024-09-25 After DRC fixes. Lots of ERC problems still
2024-09-26 Attempts to resolve wierd legacy ERC errors
2024-09-26 kicad_sch: fix annotations
    For some reason, this was largely missing annotations. KiCad will
    happily reannotate the schematics, but it renumbered everything.
    Fix annotations while keeping the same annotations.
2024-09-26 mcu: add power flags
    Add flags to the power nets to mark them as such.
2024-09-26 Updated PWR_FLAG symbols
2024-09-26 After update to Kicad V8
2024-09-26 Fixed minor DRCs
2024-09-26 Changed to USB-C connector
2024-09-26 Leave ID pin open, to signal it's a USB device
2024-09-26 Changed from SMP1330 to CLA4611 to improve performance to 6GHz
2024-09-26 Changed limiter to CLA4611. Added Schottky bias tee diode
2024-10-10 Made USB-C connector poke out 0.7mm
2024-10-10 Change USB protection to ECMF02-4CMX8
2024-10-12 Made draft production files for 2025 R10+
2024-10-24 Updated to move USB-C connector to save location as OpenSourceSDRLab's R10C
2024-11-02 Added updated schematic PDF
2024-12-01 Made design changes to indicate version 15. Correct Q3/4/5 part-no and LPF rotation
2024-12-03 Updated to latest GSG firmware, host, tools, docs files
2024-12-03 When the ADC board_revision value doesn't match an expected value, return all six bits in a special subrange for diagnostics
2024-12-03 Added U15 version detection resistors, corrected FETs and U3 rotation
2025-07-29 Updated libopencm3 to add ADC_CR_SEL
2025-08-09 Fixed clang-format warning
2025-08-09 Fixed clang-format warning (third time lucky?)
2025-08-09 Revert "Fixed clang-format warning (third time lucky?)"
    This reverts commit e39d3b243e53b276f1cc0b95172384f651f64155.
2025-08-09 Fixed clang-format warning (yet again)
